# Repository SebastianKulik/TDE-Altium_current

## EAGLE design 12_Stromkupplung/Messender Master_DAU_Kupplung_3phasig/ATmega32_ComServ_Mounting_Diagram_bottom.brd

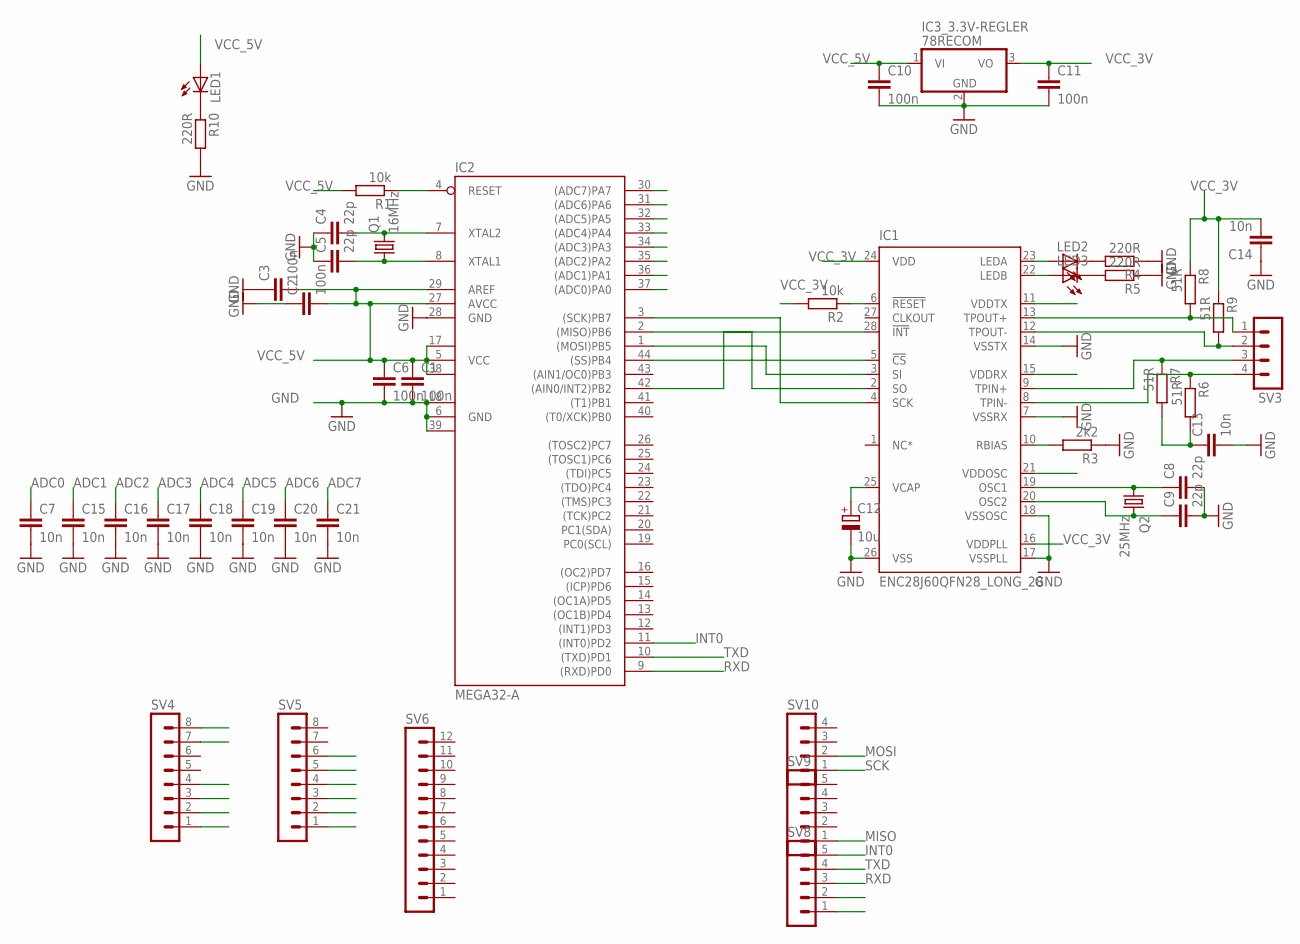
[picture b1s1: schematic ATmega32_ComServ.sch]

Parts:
C1, C2, C3, C6, C10, C11: 100n; C0805
C4, C5, C8, C9: 22p; C0805
C7, C13, C14, C15, C16, C17, C18, C19, C20, C21: 10n; C0805
C12: 10u; SMC_D
IC1: ENC28J60QFN28_LONG_28; QFN28_LONG_ERRLES
IC2: MEGA32-A; TQFP44
IC3_3.3V-REGLER: 78RECOM; RECOM_3POL
LED1, LED2, LED3: LEDCHIPLED_1206; CHIPLED_1206
Q1: 16MHz; HC49/S
Q2: 25MHz; HC49/S
R1, R2: 10k; R1206
R3: 2k2; R1206
R4, R5, R10: 220R; R1206
R6, R8, R9: 51R; R0805
R7: 51R; R1206
SV3, SV10: MA04-1
SV4, SV5: MA08-1
SV6: MA12-1
SV8, SV9: MA05-1

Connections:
1_TD+: IC1.13 (TPOUT+), R8.2, SV3.1
2_TD-: IC1.12 (TPOUT-), R9.2, SV3.2
3_RD+: IC1.9 (TPIN+), R7.1, SV3.3
6_RD-: IC1.8 (TPIN-), R6.1, SV3.4
ADC0: C7.1, IC2.37 ((ADC0)PA0), SV4.1
ADC1: C15.1, IC2.36 ((ADC1)PA1), SV4.2
ADC2: C16.1, IC2.35 ((ADC2)PA2), SV4.3
ADC3: C17.1, IC2.34 ((ADC3)PA3), SV4.4
ADC4: C18.1, IC2.33 ((ADC4)PA4), SV4.7
ADC5: C19.1, IC2.32 ((ADC5)PA5), SV4.8
ADC6: C20.1, IC2.31 ((ADC6)PA6), SV8.1
ADC7: C21.1, IC2.30 ((ADC7)PA7), SV8.2
GND: C1.2, C2.1, C3.1, C4.1, C5.1, C6.2, C7.2, C8.2, C9.2, C10.2, C11.2, C12.-, C13.2, C14.1, C15.2, C16.2, C17.2, C18.2, C19.2, C20.2, C21.2, IC1.7 (VSSRX), IC1.14 (VSSTX), IC1.17 (VSSPLL), IC1.18 (VSSOSC), IC1.26 (VSS), IC2.6 (GND), IC2.18 (GND1), IC2.28 (GND), IC2.39 (GND2), IC3_3.3V-REGLER.2 (GND), R3.1, R4.1, R5.1, R10.2, SV5.2, SV5.3, SV5.6
INT0: IC2.11 ((INT0)PD2), SV8.5
MISO: IC1.2 (SO), IC2.2 ((MISO)PB6), SV9.1
MOSI: IC1.3 (SI), IC2.1 ((MOSI)PB5), SV10.2
unnamed: C5.2, IC2.8 (XTAL1), Q1.1
unnamed: C4.2, IC2.7 (XTAL2), Q1.2
unnamed: LED1.C, R10.1
unnamed: C8.1, IC1.19 (OSC1), Q2.1
unnamed: C9.1, IC1.20 (OSC2), Q2.2
unnamed: C12.+, IC1.25 (VCAP)
unnamed: IC1.28 (!INT), IC2.42 ((AIN0/INT2)PB2)
unnamed: IC1.6 (!RESET), R2.1
unnamed: IC1.10 (RBIAS), R3.2
unnamed: LED2.C, R4.2
unnamed: IC1.23 (LEDA), LED2.A
unnamed: IC1.22 (LEDB), LED3.A
unnamed: LED3.C, R5.2
unnamed: C13.1, R6.2, R7.2
RESET: IC2.4 (RESET), R1.1, SV5.1
RXD: IC2.9 ((RXD)PD0), SV8.3
SCK: IC1.4 (SCK), IC2.3 ((SCK)PB7), SV10.1
SS: IC1.5 (!CS), IC2.44 ((SS)PB4)
TXD: IC2.10 ((TXD)PD1), SV8.4
VCC_3V: C11.1, C14.2, IC1.11 (VDDTX), IC1.15 (VDDRX), IC1.16 (VDDPLL), IC1.21 (VDDOSC), IC1.24 (VDD), IC3_3.3V-REGLER.3 (VO), R2.2, R8.1, R9.1
VCC_5V: C1.1, C2.2, C3.2, C6.1, C10.1, IC2.5 (VCC), IC2.17 (VCC1), IC2.27 (AVCC), IC2.29 (AREF), IC2.38 (VCC2), IC3_3.3V-REGLER.1 (VI), LED1.A, R1.2, SV5.4, SV5.5

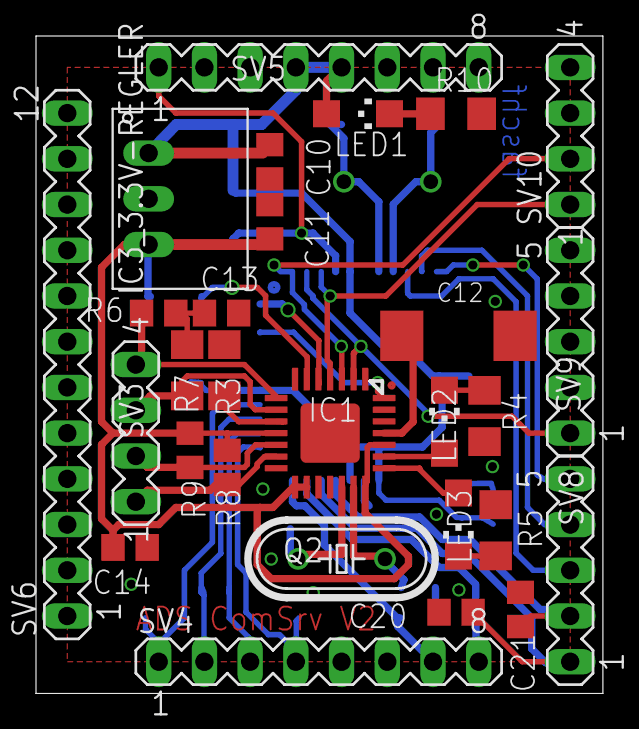
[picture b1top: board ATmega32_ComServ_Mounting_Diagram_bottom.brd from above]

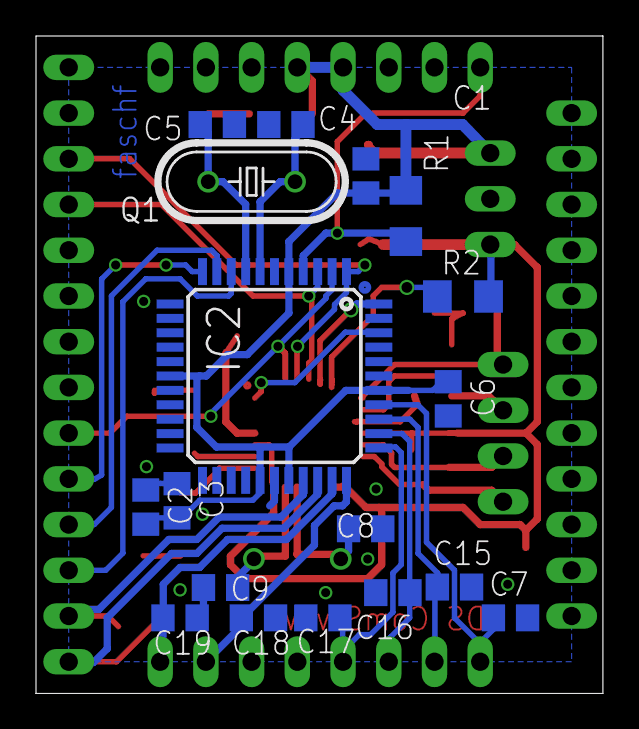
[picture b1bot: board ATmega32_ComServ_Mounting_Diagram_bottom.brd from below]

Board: 2 copper layers, 31.5 x 36.5 mm, 46 parts (18 on the bottom side), 37 nets.

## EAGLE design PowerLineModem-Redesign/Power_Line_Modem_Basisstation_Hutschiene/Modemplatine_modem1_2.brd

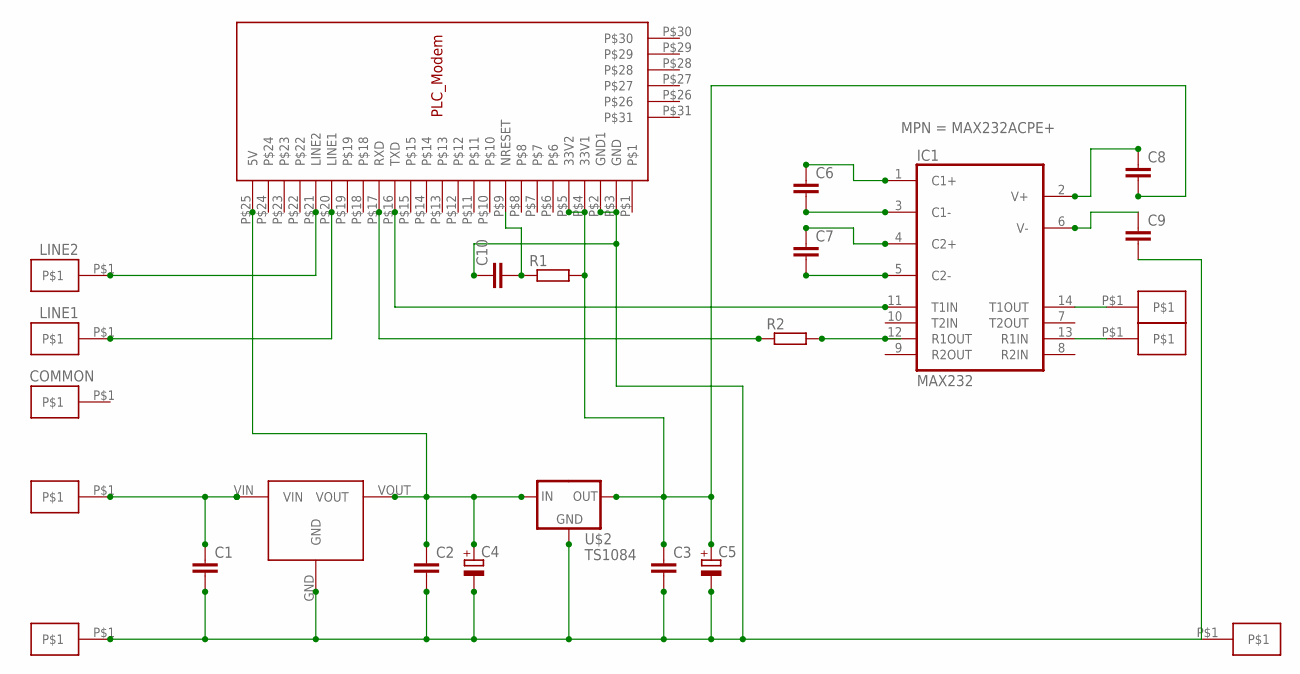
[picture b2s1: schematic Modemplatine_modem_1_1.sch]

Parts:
C1, C2, C3: C2.5/5; C2.5-5
C4, C5: CPOL-EUE2.5-5; E2,5-5
C6, C7, C8, C9, C10: C-EU025-040X050; C025-040X050
IC1: MAX232; DIL16; MPN MAX232ACPE+
LINE1, LINE2: PN4; PIN2
R1, R2: R-EU_0207/10; 0207/10
U$1: RECOM_785_05; RECOM785X
U$2: TS1084
U$3: MODEMSTECKER; MODEM_FUSS
U$4, U$5, U$6, U$7, U$8, U$11: PN4; PIN2

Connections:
GND: IC1.15 (GND)
unnamed: C1.1, U$1.VIN, U$5.P$1
unnamed: C1.2, C2.2, C3.2, C4.-, C5.-, C9.2, C10.1, U$1.GND, U$2.1GND (GND), U$3.P$2 (GND1), U$3.P$3 (GND), U$4.P$1, U$8.P$1
unnamed: C2.1, C4.+, U$1.VOUT, U$2.3IN (IN), U$3.P$25 (5V)
unnamed: C3.1, C5.+, C8.2, R1.2, U$2.2OUT (OUT), U$3.P$4 (33V1), U$3.P$5 (33V2)
unnamed: LINE2.P$1, U$3.P$21 (LINE2)
unnamed: LINE1.P$1, U$3.P$20 (LINE1)
unnamed: C6.1, IC1.1 (C1+)
unnamed: C6.2, IC1.3 (C1-)
unnamed: C7.1, IC1.4 (C2+)
unnamed: C7.2, IC1.5 (C2-)
unnamed: C8.1, IC1.2 (V+)
unnamed: C9.1, IC1.6 (V-)
unnamed: IC1.14 (T1OUT), U$6.P$1
unnamed: IC1.13 (R1IN), U$7.P$1
unnamed: IC1.11 (T1IN), U$3.P$16 (TXD)
unnamed: IC1.12 (R1OUT), R2.2
unnamed: R2.1, U$3.P$17 (RXD)
unnamed: C10.2, R1.1, U$3.P$9 (NRESET)
VCC: IC1.16 (VCC)

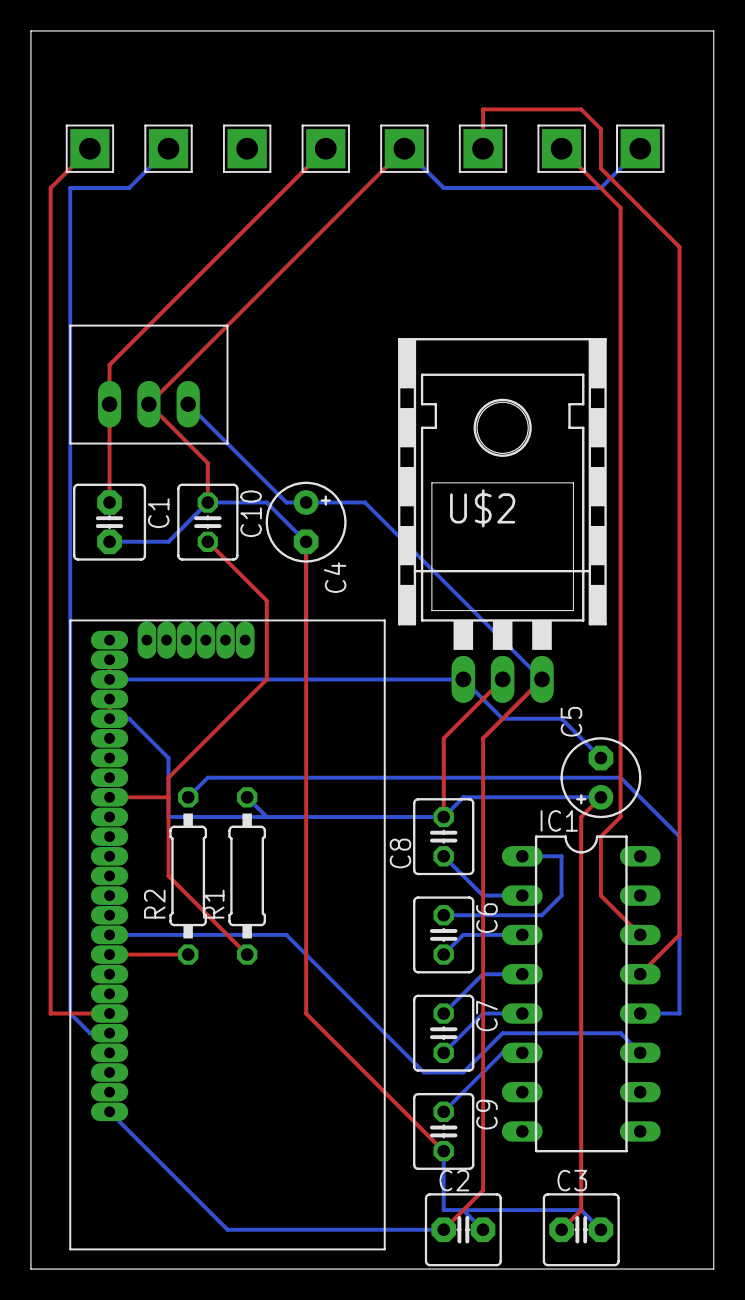
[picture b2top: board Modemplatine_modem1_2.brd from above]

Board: 2 copper layers, 44.1 x 80.0 mm, 25 parts (0 on the bottom side), 18 nets.

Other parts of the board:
E$1: A4L-LOC

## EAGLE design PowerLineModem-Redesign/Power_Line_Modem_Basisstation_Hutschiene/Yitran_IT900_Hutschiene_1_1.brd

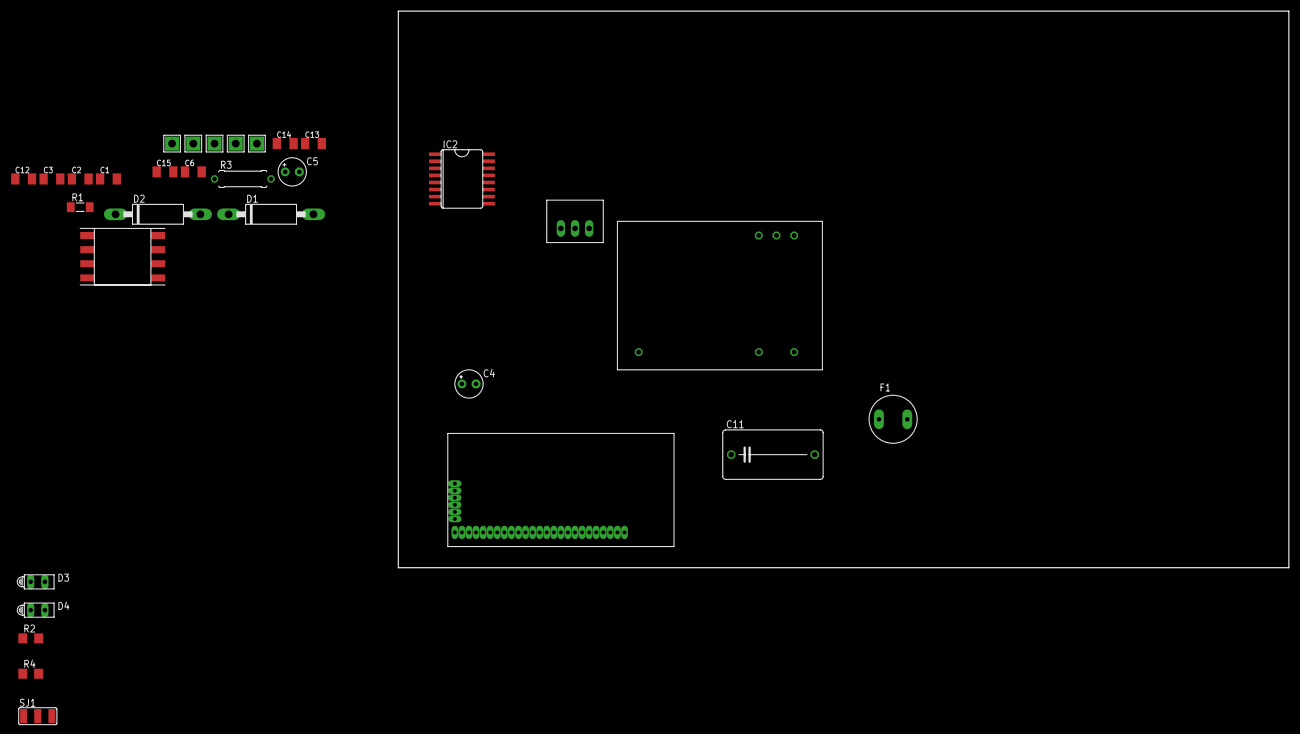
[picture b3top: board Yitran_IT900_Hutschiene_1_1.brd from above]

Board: 2 copper layers, 160.0 x 100.0 mm, 31 parts (0 on the bottom side), 24 nets, no tracks yet.

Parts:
C1, C2, C3, C6, C12, C13, C14, C15: 100n; C1206K
C4, C5: 1µ; E2,5-5
C11: 470n; C150-091X182
D1: P6KEXXC; CB417-15
D2: P6KE6V8C; CB417-15
D3: Power_3,3V rot; HLMP6
D4: TxD gruen; HLMP6
F1: 1A; TR5
GND: PN4; PIN2
IC2: MAX3232CWE; SO16L
PL1, PL2: PN4; PIN2
R1: 100k; M1406
R2, R4: 330R; R1206
R3: 470k; 0309/10
RXD: PN4; PIN2
SJ1: SJ_2W
TXD: PN4; PIN2
U$1: RECOM_783_3; RECOM785X
U$3: MODEMSTECKER; MODEM_FUSS
U$9: RECOM_RAC04_12SA; RAC04_12SA
U$10: PLC_UEBERTRAGER_V2; PLC-UEBERTRAGER_V2

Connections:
33V: C3.1, C5.+, C6.1, C12.2, R1.2, R2.2, U$1.VOUT, U$3.P$4, U$3.P$5
GND: C1.2, C2.2, C3.2, C4.-, C5.-, C6.2, C15.1, D3.K, D4.K, GND.P$1, IC2.15, SJ1.2, U$1.GND, U$3.P$2, U$3.P$3, U$9.GND
L: C11.1, D1.C, F1.2, R3.1, U$9.L
N: D1.A, D2.A, PL2.P$1, U$9.N, U$10.8N
unnamed: F1.1, PL1.P$1
unnamed: C11.2, D2.C, R3.2, U$10.L5
unnamed: C2.1, C4.+, U$1.VIN, U$9.+VO
unnamed: D3.A, R2.1
unnamed: U$3.P$21, U$10.1LINE1
unnamed: U$3.P$20, U$10.4LINE2
unnamed: C13.1, IC2.1
unnamed: C13.2, IC2.3
unnamed: C14.1, IC2.4
unnamed: C14.2, IC2.5
unnamed: C12.1, IC2.2
unnamed: C1.1, IC2.6
unnamed: D4.A, R4.1
unnamed: SJ1.1, U$10.2
unnamed: SJ1.3, U$10.3
unnamed: IC2.11, U$3.P$16
unnamed: IC2.12, U$3.P$17
unnamed: C15.2, R1.1, U$3.P$9
RXD: IC2.13, RXD.P$1
TXD: IC2.14, R4.2, TXD.P$1
